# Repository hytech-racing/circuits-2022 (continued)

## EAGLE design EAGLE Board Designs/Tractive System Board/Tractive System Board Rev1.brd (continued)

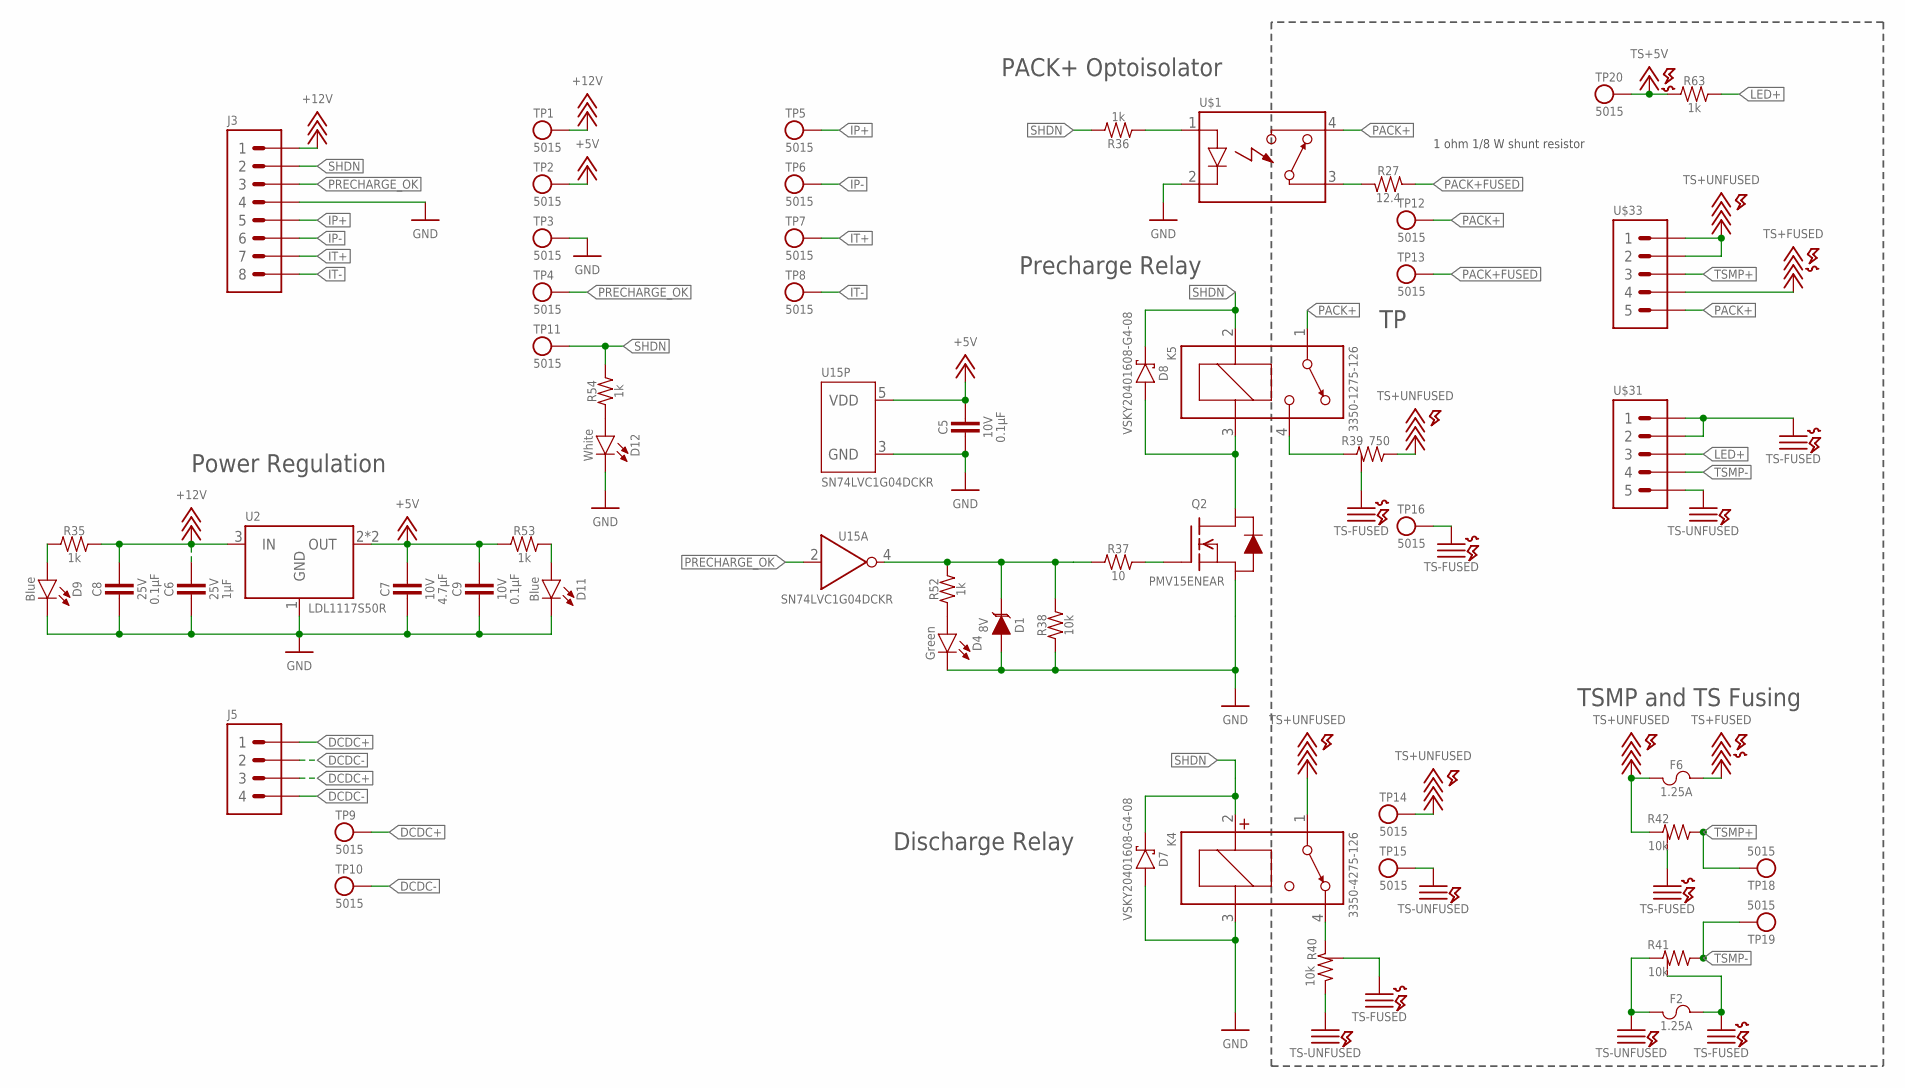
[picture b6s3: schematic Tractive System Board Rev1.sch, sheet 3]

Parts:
C5, C9: CAPACITOR_0603_10V_0.1UF; 0603-CAP
C6: CAPACITOR_0603_25V_1UF; 0603-CAP
C7: CAPACITOR_0603_10V_4.7UF; 0603-CAP
C8: CAPACITOR_0603_25V_0.1UF; 0603-CAP
D1: TVS_8V; SOT-23
D4: LED_0603_GREEN; 0603-LED
D7, D8: SCHOTTKY; CLP1608-2L
D9, D11: LED_0603_BLUE; 0603-LED
D12: LED_0603_WHITE; 0603-LED
F2, F6: FUSE_0885_1.25; 0885
J3: CONNECTOR-8_MF_T_V_; MOLEX_MICROFIT_PTH_VERTICAL_08_DUAL
J5: CONNECTOR-4__; MOLEX_MICROFIT_PTH_VERTICAL_04_DUAL
K4: RELAY_SPST_NC_POLARIZED_3550_12; 335X
K5: RELAY_SPST_NO_3550_12; 335X
Q2: TRANSISTOR_N_MOS__PMV15ENEA; SOT-23
R27: RESISTOR_0805_12.4; 0805-RES
R35, R36, R52, R53, R54, R63: RESISTOR_0603_1K; 0603-RES
R37: RESISTOR_0603_10; 0603-RES
R38: RESISTOR_0603_10K; 0603-RES
R39: RESISTOR_GND_750; B20
R40, R41, R42: RESISTOR_GND_10K; B20
TP1, TP2, TP3, TP4, TP5, TP6, TP7, TP8, TP9, TP10, TP11, TP12, TP13, TP14, TP15, TP16, TP18, TP19, TP20: TEST_POINT; MICRO_MINIATURE
U2: VOLTAGE_REGULATOR_SOT223_5V; SOT223
U15: LOGICGATE_INVERTER_DCKR; SC-70-5
U$1: RELAY_SOLIDSTATE_NO_AG; DIP-4_AIRGAP
U$31: CONNECTOR-5_MICRO_V6S_; MOLEX_MICROFIT_PTH_VERTICAL_06_SINGLE_SPACED
U$33: CONNECTOR-5_MICRO_V7S_; MOLEX_MICROFIT_PTH_VERTICAL_07_SINGLE_SPACED

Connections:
+5V: C5.1, C7.1, C9.1, R53.1, TP2.1, U2.2 (OUT), U2.4 (OUT), U15.5 (VDD); also elsewhere on the board
+12V: C6.1, C8.1, J3.1, R35.2, TP1.1, U2.3 (IN)
DCDC+: J5.1, J5.3, TP9.1; also elsewhere on the board
DCDC-: J5.2, J5.4, TP10.1; also elsewhere on the board
GND: C5.2, C6.2, C7.2, C8.2, C9.2, D1.1 (A), D4.1 (C), D7.2 (A), D9.1 (C), D11.1 (C), D12.1 (C), J3.4, K4.3 (COIL-), Q2.2 (S), R38.1, TP3.1, U2.1 (GND), U15.3 (GND), U$1.2 (CONTROL-); also elsewhere on the board
IP+: J3.5, TP5.1; also elsewhere on the board
IP-: J3.6, TP6.1; also elsewhere on the board
IT+: J3.7, TP7.1; also elsewhere on the board
IT-: J3.8, TP8.1; also elsewhere on the board
LED+: R63.2, U$31.3
unnamed: Q2.1 (G), R37.2
unnamed: D4.2 (A), R52.1
unnamed: D9.2 (A), R35.1
unnamed: D11.2 (A), R53.2
unnamed: D12.2 (A), R54.1
unnamed: D8.2 (A), K5.3 (COIL-), Q2.3 (D)
unnamed: K5.4 (CONTACT2), R39.1
unnamed: K4.4 (CONTACT2), R40.1
unnamed: D1.3 (C), R37.1, R38.2, R52.2, U15.4 (!IN)
unnamed: R36.1, U$1.1 (CONTROL+)
unnamed: R27.2, U$1.3 (CONTACT1)
PACK+: K5.1 (CONTACT1), TP12.1, U$1.4 (CONTACT2), U$33.5
PACK+FUSED: R27.1, TP13.1; also elsewhere on the board
PRECHARGE_OK: J3.3, TP4.1, U15.2 (IN); also elsewhere on the board
SHDN: D7.1 (C), D8.1 (C), J3.2, K4.2 (COIL+), K5.2 (COIL+), R36.2, R54.2, TP11.1
TS+5V: R63.1, TP20.1; also elsewhere on the board
TS+FUSED: F6.2, U$33.4; also elsewhere on the board
TS+UNFUSED: F6.1, K4.1 (CONTACT1), R39.2, R42.1, TP14.1, U$33.1, U$33.2
TS-FUSED: F2.2, R39.3, R39.4 (3), R39.5 (3), R39.6 (3), R40.3, R40.4 (3), R40.5 (3), R40.6 (3), R41.3, R41.4 (3), R41.5 (3), R41.6 (3), R42.3, R42.4 (3), R42.5 (3), R42.6 (3), TP16.1, U$31.1, U$31.2; also elsewhere on the board
TS-UNFUSED: F2.1, R40.2, R41.1, TP15.1, U$31.5
TSMP+: R42.2, TP18.1, U$33.3
TSMP-: R41.2, TP19.1, U$31.4

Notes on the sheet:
PACK+ Optoisolator
Precharge Relay
Discharge Relay
TSMP and TS Fusing
Power Regulation
1 ohm 1/8 W shunt resistor

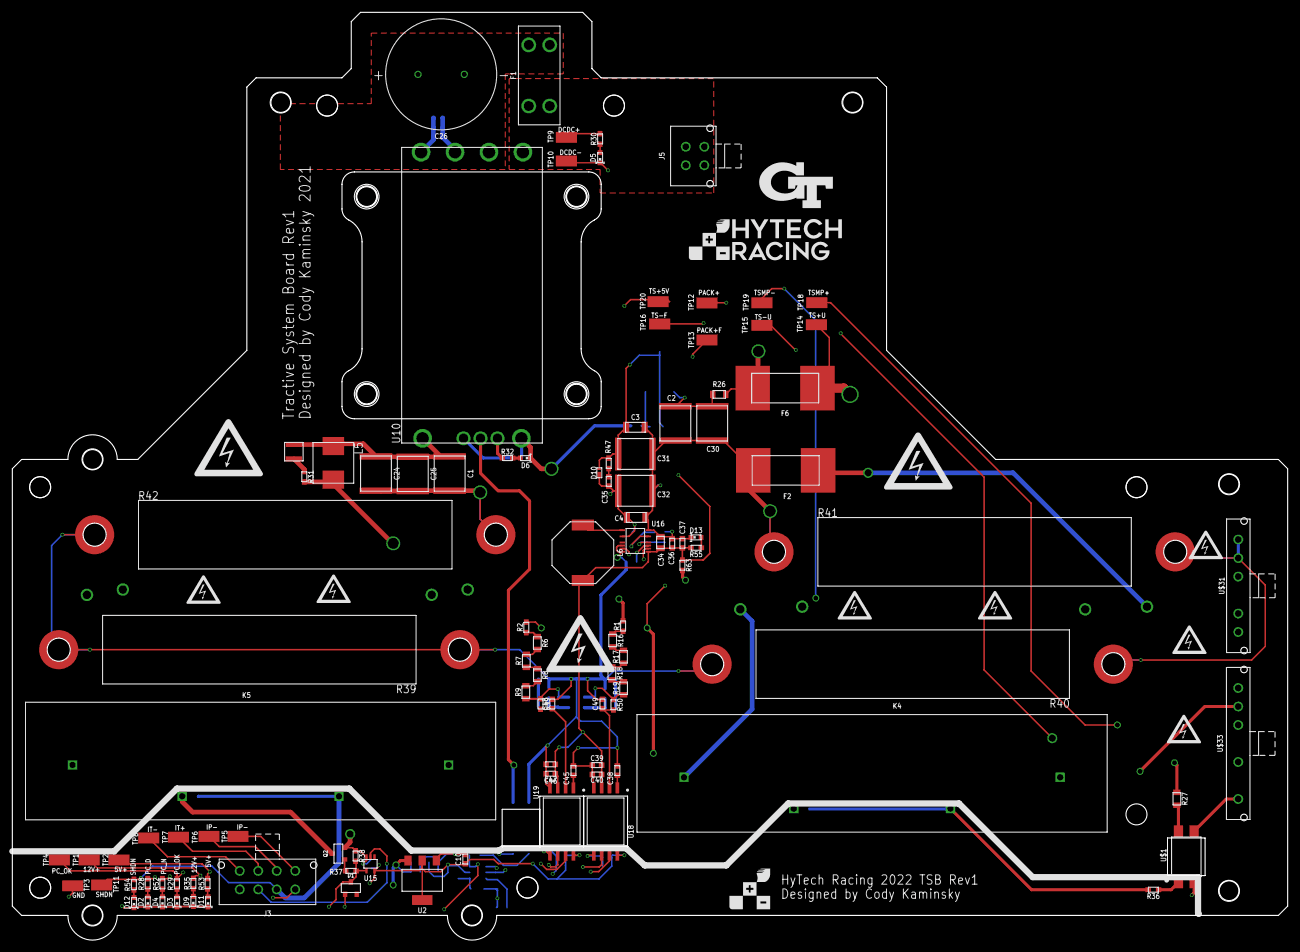
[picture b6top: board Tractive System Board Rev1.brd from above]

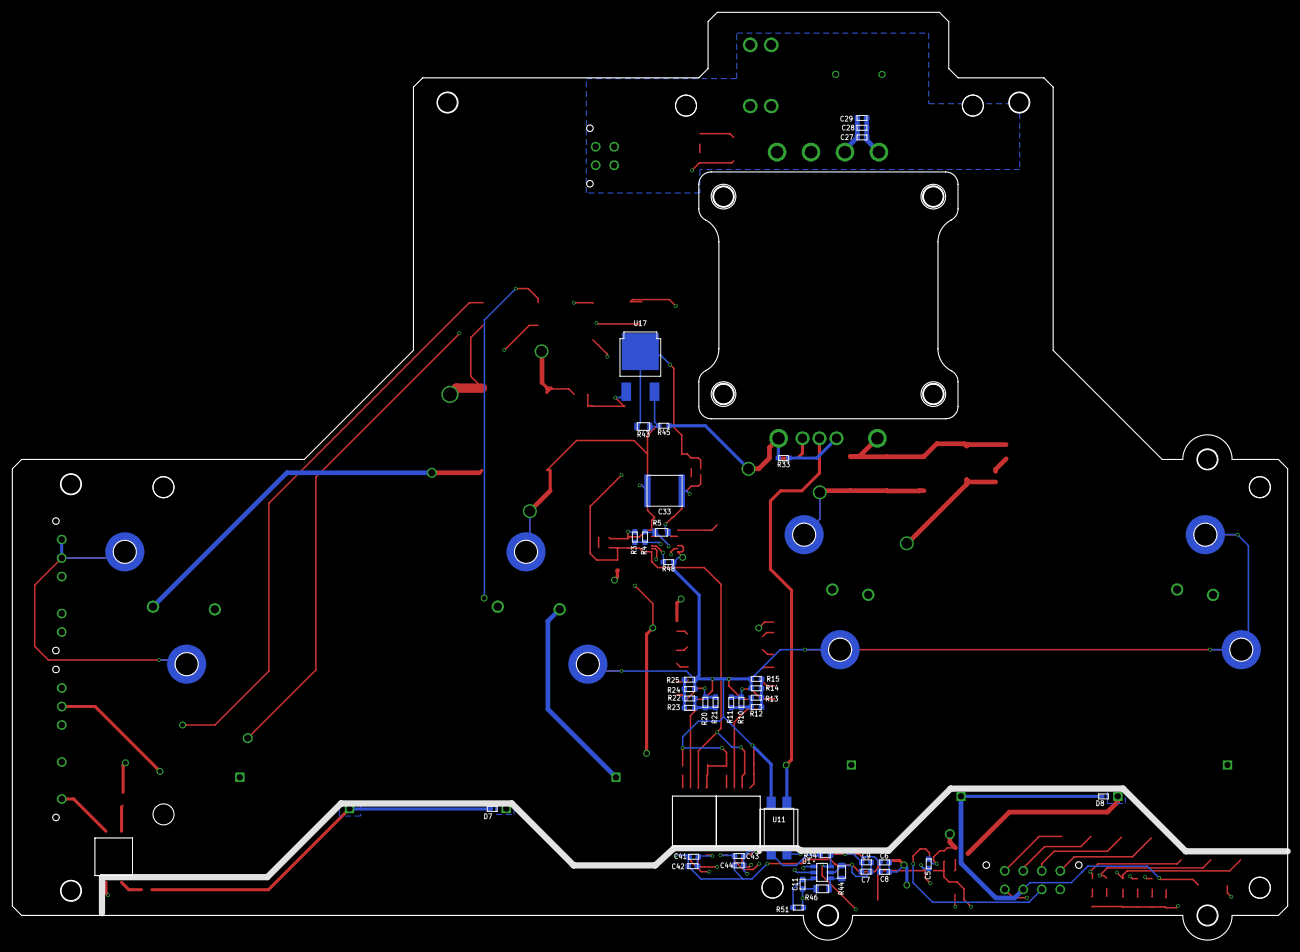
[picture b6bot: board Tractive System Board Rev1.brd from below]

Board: 4 copper layers, 206.7 x 150.3 mm, 193 parts (42 on the bottom side), 75 nets.

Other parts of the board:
U$5, U$6, U$7, U$8, U$9, U$10, U$11, U$12, U$13, U$14, U$15, U$26, U$34, U$35, U$37, U$38, U$39, U$41: MOUNTING_M3
U$43, U$44, U$45, U$46, U$47, U$49, U$50: HV_0.50"
U$48, U$51, U$52: HV_1.00"
U$53: LOGO_HYTECH_1.0"
U$54: LOGO_GT_0.50"
U$55: LOGO_HYTECH_SQUARE_0.28"
U$56, U$57, U$58, U$59, U$60, U$61, U$62: GLV
U$63, U$64, U$65, U$66, U$67, U$68, U$69: TS

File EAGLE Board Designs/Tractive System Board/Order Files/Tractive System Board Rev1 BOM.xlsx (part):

Qty | Value | Device | Package | Parts | Description | CAPACITANCE | COLOR | CURRENT | CURRENT_RATED | CURRENT_SATURATION | DCR | DKPN | INDUCTANCE | MANUFACTURER | MOPN | MPN | POWER | RESISTANCE | TOLERANCE | VOLTAGE | VOLTAGE_CONTINUOUS | VOLTAGE_MAX | Column1
6 | CAPACITOR_0603_10V_0.1UF | CAPACITOR_0603_10V_0.1UF | 0603-CAP | C5, C9, C10, C11, C42, C43 | Capacitor, Non-Polarized | 0.1µF |  |  |  |  |  | 720-1688-1-ND |  | Vishay Vitramon | 77-VJ0603Y104JXQPBC | VJ0603Y104JXQPW1BC |  |  | 0.05 | 10V
3 | CAPACITOR_0603_10V_10NF | CAPACITOR_0603_10V_10NF | 0603-CAP | C35, C48, C49 | Capacitor, Non-Polarized | 10nF |  |  |  |  |  | 311-4054-1-ND |  | Yageo | 603-CC603KRX7R6BB103 | CC0603KRX7R6BB103 |  |  | 0.1 | 10V
8 | CAPACITOR_0603_10V_1UF | CAPACITOR_0603_10V_1UF | 0603-CAP | C38, C39, C40, C41, C44, C45, C46, C47 | Capacitor, Non-Polarized | 1µF |  |  |  |  |  | 311-1796-1-ND |  | Yageo | 603-CC603KRX7R6BB105 | CC0603KRX7R6BB105 |  |  | 0.1 | 10V
1 | CAPACITOR_0603_10V_4.7UF | CAPACITOR_0603_10V_4.7UF | 0603-CAP | C7 | Capacitor, Non-Polarized | 4.7µF |  |  |  |  |  | 1276-1044-1-ND |  | Samsung Electro-Mechanics | 187-CL10A475KP8NNNC | CL10A475KP8NNNC |  |  | 0.1 | 10V
2 | CAPACITOR_0603_25V_0.1UF | CAPACITOR_0603_25V_0.1UF | 0603-CAP | C8, C37 | Capacitor, Non-Polarized | 0.1µF |  |  |  |  |  | 1276-1006-1-ND |  | Samsung Electro-Mechanics | 187-CL10B104KA8NNNC | CL10B104KA8NNNC |  |  | 0.1 | 25V
1 | CAPACITOR_0603_25V_10UF | CAPACITOR_0603_25V_10UF | 0603-CAP | C27 | Capacitor, Non-Polarized | 10µF |  |  |  |  |  | 490-7202-1-ND |  | Murata Electronics | 81-GRM188R61E106MA3D | GRM188R61E106MA73D |  |  | 0.2 | 25V
3 | CAPACITOR_0603_25V_1UF | CAPACITOR_0603_25V_1UF | 0603-CAP | C6, C28, C36 | Capacitor, Non-Polarized | 1µF |  |  |  |  |  | 1276-1184-1-ND |  | Samsung Electro-Mechanics | 187-CL10B105KA8NNNC | CL10B105KA8NNNC |  |  | 0.1 | 25V
1 | CAPACITOR_0603_35V_0.1UF | CAPACITOR_0603_35V_0.1UF | 0603-CAP | C29 | Capacitor, Non-Polarized | 0.1µF |  |  |  |  |  | 587-3354-1-ND |  | Taiyo Yuden | 963-GMK107B7104KAHT | GMK107B7104KAHT |  |  | 0.1 | 35V
1 | CAPACITOR_0805_25V_22UF | CAPACITOR_0805_25V_22UF | 0805-CAP | C34 | Capacitor, Non-Polarized | 22µF |  |  |  |  |  | 311-1903-1-ND |  | Yageo | 603-CC805MKX5R8BB226 | CC0805MKX5R8BB226 |  |  | 0.2 | 25V
2 | CAPACITOR_1206_250V_0.1UF | CAPACITOR_1206_250V_0.1UF | 1206-CAP | C3, C4 | Capacitor, Non-Polarized | 0.1uF |  |  |  |  |  | 445-6079-2-ND |  | TDK Corporation | 810-C3216X7R2E104KT5 | C3216X7R2E104K160AM |  |  | 0.1 | 250V
3 | CAPACITOR_2220_250V_1UF | CAPACITOR_2220_250V_1UF | 2220-CAP | C31, C32, C33 | Capacitor, Non-Polarized | 1µF |  |  |  |  |  | 445-2304-2-ND |  | TDK Corporation | 810-C5750X7R2E105K | C5750X7R2E105K230KA |  |  | 0.1 | 250V
2 | CAPACITOR_2220_630V_0.1UF | CAPACITOR_2220_630V_0.1UF | 2220-CAP | C1, C2 | Capacitor, Non-Polarized | 0.1uF |  |  |  |  |  | 445-11980-2-ND |  | TDK Coporation | 810-C5750CH2J104K2KC | C5750CH2J104K280KC |  |  | 0.1 | 630V
3 | CAPACITOR_2220_630V_1UF | CAPACITOR_2220_630V_1UF | 2220-CAP | C24, C25, C30 | Capacitor, Non-Polarized | 1µF |  |  |  |  |  | 1608-2220Y6300105KXTWS2CT-ND |  | Knowles Syfer | 843-2220Y63105KXTWS2 | 2220Y6300105KXTWS2 |  |  | 0.1 | 630V
1 | CAPACITOR_POLAR__3600UF | CAPACITOR_POLAR__3600UF | EKYC*MM | C26 |  | 3600uF |  |  |  |  |  | 565-EKYC250ELL362ML20S-ND |  | United Chemi-con | 661-YC250ELL362ML20S | EKYC250ELL362ML20S |  |  |  | 25V
1 | CONNECTOR-4__ | CONNECTOR-4__ | MOLEX_MICROFIT_PTH_VERTICAL_04_DUAL | J5 |  |  |  |  |  |  |  |  |  | Molex |  | 2068320423
1 | CONNECTOR-5_MICRO_V6S_ | CONNECTOR-5_MICRO_V6S_ | MOLEX_MICROFIT_PTH_VERTICAL_06_SINGLE_SPACED | U$31 |  |  |  |  |  |  |  |  |  | Molex |  | 2165713006
1 | CONNECTOR-5_MICRO_V7S_ | CONNECTOR-5_MICRO_V7S_ | MOLEX_MICROFIT_PTH_VERTICAL_07_SINGLE_SPACED | U$33 |  |  |  |  |  |  |  |  |  | Molex |  | 2165713007
1 | CONNECTOR-8_MF_T_V_ | CONNECTOR-8_MF_T_V_ | MOLEX_MICROFIT_PTH_VERTICAL_08_DUAL | J3 | 8 Pin Connector |  |  |  |  |  |  |  |  | Molex |  | 2068320823
1 | DCM4623TD2J13D0T70 | DCM4623TD2J13D0T70 | DCM4623 | U10 | 400W 300V to 12V step-down DC-DC converter |  |  |  |  |  |  | 1102-DCM4623TD2J13D0T70-ND |  | Vicor | 492-DCM4623D2J13D0T7 | DCM4623TD2J13D0T70
2 | FUSE_0885_1.25 | FUSE_0885_1.25 | 0885 | F2, F6 | Fuse |  |  | 1.25A |  |  |  | F10986CT-ND |  | Littelfuse Inc. | 576-08851.25DR | 08851.25DR |  |  |  | 500V
1 | FUSE_MB_10 | FUSE_MB_10 | MINI-BLADE_FUSE_HOLDER | F1 | Fuse |  |  | 10A |  |  |  | F991-ND |  | Littelfuse Inc. | 576-0297010.WXNV | 0297010.WXNV |  |  |  | 32V
1 | INDUCTOR_PA4334_3.6UH | INDUCTOR_PA4334_3.6UH | PA4334 | L4 | Inductor |  |  |  | 1.6A | 1A | 0.13 | 553-3508-2-ND | 3.6uH | Pulse Electonics Company | 673-PA4334362NLT | PA4334.362NLT |  |  | 0.2
1 | INDUCTOR_SRU1048_330UH | INDUCTOR_SRU1048_330UH | SRU1048 | L6 | Inductor |  |  |  | 0.65A | 0.52A | 0.640Ω | SRU1048-331YTR-ND | 330µH | Bourns Inc. | 652-SRU1048-331Y | SRU1048-331Y |  |  | 0.3
1 | INDUCTOR_WELMHI_56UH | INDUCTOR_WELMHI_56UH | WE-LMHI | L5 | Inductor |  |  |  | 1.4A | 1.4A | 342m | 732-11454-2-ND | 56uH | Wurth Elektronik | 710-74437349560 | 74437349560 |  |  | 0.2
2 | ISO224B_AIRGAP | ISO224B_AIRGAP | SOIC-08(WIDE,0.295)-AIRGAP" | U18, U19 | ISO224*: Isolated precision amplifier |  |  |  |  |  |  | 296-52316-1-ND |  | Texas Instruments | 595-ISO224BDWVR | ISO224BDWVR
3 | LED_0603_BLUE | LED_0603_BLUE | 0603-LED | D9, D11, D13 | LED |  | Blue |  |  |  |  | 754-1789-1-ND |  | Kingbright | 604-APT1608VBC/D | APT1608VBC/D
1 | LED_0603_GREEN | LED_0603_GREEN | 0603-LED | D4 | LED |  | Green |  |  |  |  | 754-1790-1-ND |  | Kingbright | 604-APT1608ZGCK | APT1608ZGCK
1 | LED_0603_ORANGE | LED_0603_ORANGE | 0603-LED | D2 | LED |  | Orange |  |  |  |  | 754-1120-1-ND |  | Kingbright | 604-APT1608SECK | APT1608SECK
1 | LED_0603_RED | LED_0603_RED | 0603-LED | D6 | LED |  | Red |  |  |  |  | 754-1786-1-ND |  | Kingbright | 604-APT1608SECKJ3PRV | APT1608SECK/J3-PRV
2 | LED_0603_WHITE | LED_0603_WHITE | 0603-LED | D5, D12 | LED |  | White |  |  |  |  | SM0603UWC-ND |  | Bivar Inc. | 749-SM0603UWC | SM0603UWC
1 | LED_0603_YELLOW | LED_0603_YELLOW | 0603-LED | D3 | LED |  | Yellow |  |  |  |  | 754-1788-1-ND |  | Kingbright | 604-APT1608SYCK/J3-PRV | APT1608SYCK/J3-PRV
1 | LOGICGATE_INVERTER_DCKR | LOGICGATE_INVERTER_DCKR | SC-70-5 | U15 | Inverter |  |  |  |  |  |  | 2156-SN74LVC1G04DCKR-ND |  | Texas Instruments | 595-SN74LVC1G04DCKR | SN74LVC1G04DCKR
1 | LTC3639 | LTC3639 | MSE16(12) | U16 | LTC3639 |  |  |  |  |  |  | LTC3639EMSE#TRPBFTR-ND |  | Analog Devices Inc. | 584-LTC3639EMSETRPBF | LTC3639EMSE#TRPBF
1 | LTC6994_1 | LTC6994_1 | SOT-23-6 | U1 | Analog Electronics Delay IC |  |  |  |  |  |  | 505-LTC6994CS6-1#TRMPBFTR-ND |  | Analog Electronics | 584-C6994CS6-1TRMPBF | LTC6994CS6-1#TRMPBF
1 | RELAY_SOLIDSTATE_NC_AG | RELAY_SOLIDSTATE_NC_AG | DIP-4_AIRGAP | U11 | Normally Closed Solid-State Relay |  |  |  |  |  |  | 255-2897-ND |  | Panasonic Industrial Devices | 769-AQY414EHA | AQY414EHA
1 | RELAY_SOLIDSTATE_NO_AG | RELAY_SOLIDSTATE_NO_AG | DIP-4_AIRGAP | U$1 | Normally Open Solid-State Relay |  |  |  |  |  |  | 255-1436-5-ND |  | Panasonic Inustrial Devices | 769-AQY214EHA | AQY214EHA
1 | RELAY_SPST_NC_POLARIZED_3550_12 | RELAY_SPST_NC_POLARIZED_3550_12 | 335X | K4 | Single Pole, Single Throw Normally Closed Polarized Relay |  |  |  |  |  |  | 1835-1040-ND |  | Comus International |  | 3350-4275-126
1 | RELAY_SPST_NO_3550_12 | RELAY_SPST_NO_3550_12 | 335X | K5 | Single Pole, Single Throw Relay Normally Open |  |  |  |  |  |  | 1835-1037-ND |  | Comus International |  | 3350-1275-126
1 | RESISTOR_0603_1.62 | RESISTOR_0603_1.62 | 0603-RES | R31 | Resistor |  |  |  |  |  |  | 1712-CPF0603B1R62E1TR-ND |  | TE Conductivity Passive Product | 279-CPF0603B1R62E1 | CPF0603B1R62E1 | 0.1W | 1.62 | 1E-3 |  | 0.51V | 50V
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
